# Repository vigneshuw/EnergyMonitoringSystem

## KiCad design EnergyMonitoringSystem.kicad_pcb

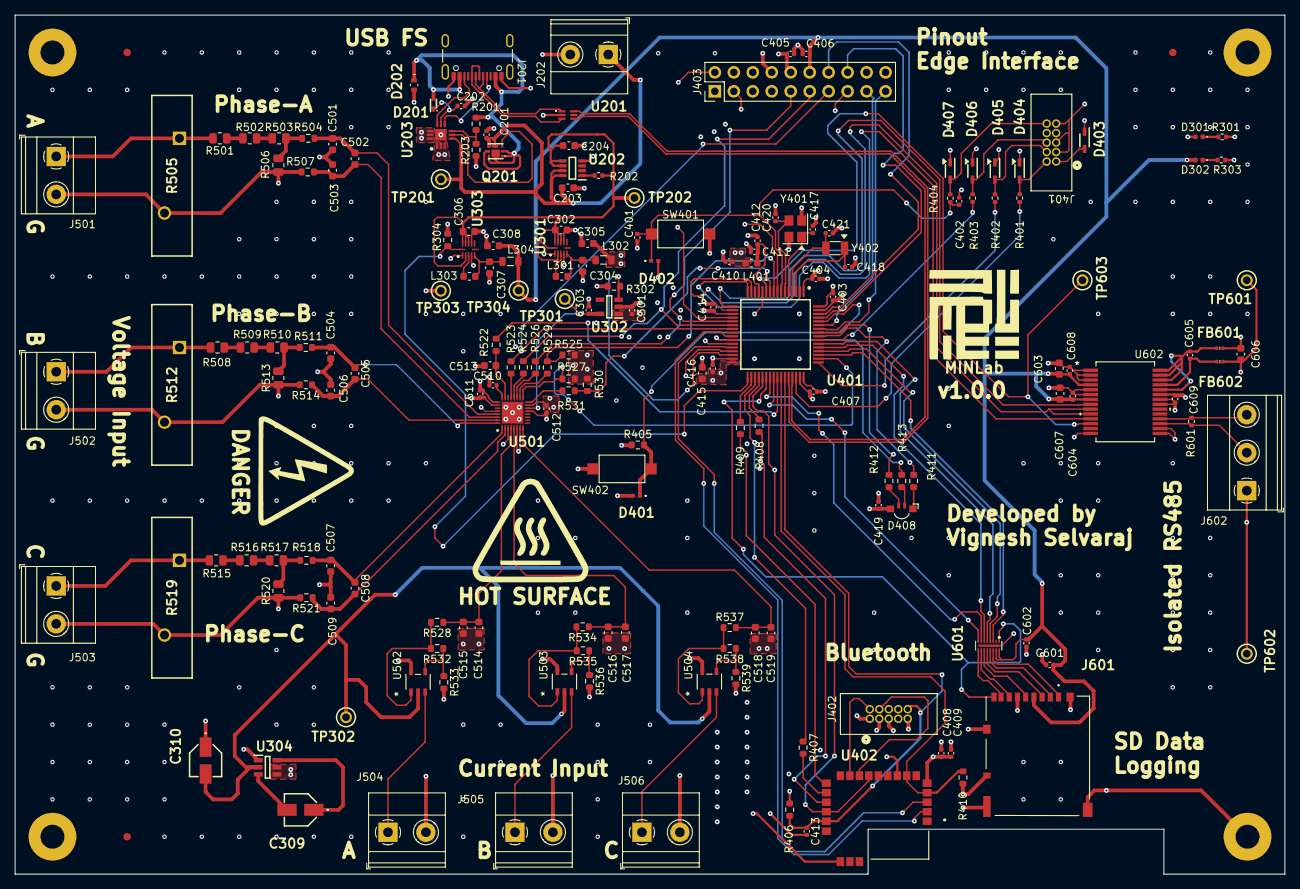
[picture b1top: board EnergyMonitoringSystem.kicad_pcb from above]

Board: 6 copper layers, 170.0 x 115.0 mm, 191 parts (0 on the bottom side), 136 nets.

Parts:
C201, C202, C401, C402, C403, C404, C405, C406, C407, C409, C413, C414, C415, C419, C601, C602: 100n; C_0402_1005Metric
C203, C204, C302, C306, C416, C603, C606, C607: 10u; C_0603_1608Metric
C301, C303, C410, C411, C511, C512: 1u; C_0402_1005Metric
C304, C305, C307, C308: 47u; C_0603_1608Metric
C309, C310: 10u; 10SVPS10M
C408: 2u2; C_0402_1005Metric
C412: 10n; C_0402_1005Metric
C417, C420: 6p8; C_0402_1005Metric
C418, C421: 5p6; C_0402_1005Metric
C501, C503, C504, C506, C507, C509, C513, C514, C516, C518: 10p; C_0603_1608Metric
C502, C505, C508, C515, C517, C519: 6800p; C_0603_1608Metric
C510: 220n; C_0402_1005Metric
C604, C605, C608, C609: 0.1u; C_0402_1005Metric
D201: BAT30KFILM
D202: ESDA7P60-1U1M
D301, D302: LED; LED_0402_1005Metric
D401, D402: ESDALC6V1-1M2; ESDALC6V11M2
D403, D404, D405, D406, D407: PESD3V3L1BA,115; PESD3V3L1BA_115-SOD-323-2
D408: LED_RAGB; LED_Kingbright_APFA3010_3x1.5mm_Horizontal
FB601, FB602: FerriteBead; BLM15HD182SN1D
FM201, FM202, FM203: Fiducial; Fiducial_1mm_Mask2mm
H201, H202, H203, H204: MountingHole_Pad; MountingHole_3.2mm_M3_Pad
J201: USB_C_Receptacle_USB2.0_16P; USB_C_Receptacle_GCT_USB4105-xx-A_16P_TopMnt_Horizontal
J202, J501, J502, J503, J504, J505, J506: Screw_Terminal_01x02; TerminalBlock_Phoenix_MKDS-1,5-2-5.08_1x02_P5.08mm_Horizont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
J401, J402: Conn_02x05_Counter_Clockwise; 62701021621
J403: Conn_02x08_Counter_Clockwise; PinHeader_2x10_P2.54mm_Vertical
J601: DM3AT-SF-PEJM5_40_; DM3ATSFPEJM540
J602: Screw_Terminal_01x03; TerminalBlock_Phoenix_MKDS-1,5-3-5.08_1x03_P5.08mm_Horizont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
L301, L303: 2u2; L_0603_1608Metric
L302, L304: 10u; L_0805_2012Metric
L401: 10n; L_0603_1608Metric
Q201: STL6N3LLH6
R201, R405, R525, R533, R536, R539: 10k; R_0603_1608Metric
R202, R601: 120R; R_0402_1005Metric
R203: 2k7; R_0603_1608Metric
R301, R303: 220R; R_0402_1005Metric
R302, R304, R527, R530: 100k; R_0603_1608Metric
R401, R402, R403, R404: 49R9; R_0402_1005Metric
R406: 4k7; R_0603_1608Metric
R407, R408, R409: 22R; R_0603_1608Metric
R410: 47k; R_0603_1608Metric
R411, R412, R413, R504, R507, R511, R514, R518, R521: 1k; R_0603_1608Metric
R501, R502, R503, R508, R509, R510, R515, R516, R517: 330k; R_0805_2012Metric
R505, R512, R519: R_Variable; B72220S0271K101
R506, R513, R520: 750R; R_0805_2012Metric
R522, R523, R524, R526, R529, R531: 33R; R_0603_1608Metric
R528, R534, R537: 2k; R_0603_1608Metric
R532, R535, R538: 15k; R_0603_1608Metric
SW401, SW402: SW_Push; SW_SPST_CK_RS282G05A3
TP201, TP202, TP301, TP302, TP303, TP304, TP601, TP602, TP603: TestPoint; 5000
U201: USBLC6-2P6; USBLC62P6-SOT666-6
U202: STEF05SGR; STEF05SGR-TSOT23-8L
U203: TCPP01-M12; TCPP01-M12-QFN-12L
U301, U303: ST1PS02CQTR
U302: LDLN025M12R; LDLN025M12R-SOT-23-5
U304: LM2664M6_NOPB; LM2664M6_NOPB-SOT-23-6
U401: STM32F103RGT6; STM32F103RGT6-LQFP-64
U402: BLUENRG-M2SA
U501: ADS131M08IRSNR; ADS131M08IRSNR-QFN40
U502, U503, U504: TSV911ILT; TSV911ILT_SOT23-5
U601: EMIF06-MSD02N16
U602: ADM2565EBRNZ; ADM2565EBRNZ-SOIC-28
Y401: 16MHz; Crystal_SMD_3225-4Pin_3.2x2.5mm
Y402: 32.768KHz; Crystal_SMD_3215-2Pin_3.2x1.5mm

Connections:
+1V2: C303.1, TP301.1, U302.5 (OUT), U501.14 (REFIN)
+5V: C204.1, C302.1, C306.1, R202.1, TP202.1, U202.5 (SOURCE_1), U202.6 (SOURCE_2), U301.2 (VIN), U301.9 (D0), U301.10 (D1), U301.11 (D2), U301.12 (EN), U303.2 (VIN), U303.9 (D0), U303.10 (D1), U303.11 (D2)
+5V_EXT: C201.1, C203.1, J202.1, Q201.4 (S_1), Q201.8 (S_2), TP201.1, U202.7 (VCC_1), U202.8 (VCC_2), U203.4 (SOURCE)
+DCDC_1: C301.1, C305.1, C403.1, C404.1, C405.1, C407.1, C408.1, C409.1, C410.1, C414.1, C415.1, C416.1, C419.1, C511.2, C512.2, D301.2 (A), D403.2 (K2), D408.2 (A), J401.1, J402.1, J403.10, L302.2, L401.1, R406.2, R525.2, R527.2, R530.2, SW402.2, TP303.1, U302.1 (IN), U304.4 (SD), U304.5 (V+), U401.1 (VBAT), U401.19 (VDD_4), U401.32 (VDD_1), U401.48 (VDD_2), U401.64 (VDD_3), U402.5 (VIN), U501.15 (AVDD), U501.26 (DVDD), U502.5 (VCC+), U503.5 (VCC+), U504.5 (VCC+)
+DCDC_2: C308.1, C406.1, C601.1, C602.1, C603.1, C604.1, C607.2, C608.2, D302.2 (A), J403.12, J601.4 (VDD), L304.2, TP304.1, U601.15 (VCC), U601.16 (RDATA_VCC), U602.4 (VCC), U602.7 (VIO)
+VBUSc: D201.2 (A), D202.1 (K), J201.A4 (VBUS), J201.A9 (VBUS), J201.B4 (VBUS), J201.B9 (VBUS), Q201.1 (D_1), Q201.2 (D_2), Q201.5 (D_3), Q201.6 (D_4), Q201.7 (D_5), R201.1
+V_ISO: C606.2, C609.1, FB602.2, TP601.1, U602.23 (VISOIN)
-DCDC_1: C310.2, TP302.1, U304.2 (OUT), U502.2 (VCC-), U503.2 (VCC-), U504.2 (VCC-)
/ADC/CLKIN_ADS_T: C513.1, R522.2, U501.23 (XTAL1_CLKIN)
/ADC/CT_PhaseA_Amp_OUT: R528.2, R532.2, U502.1 (OUT)
/ADC/CT_PhaseA_IN: J504.1, U502.3 (IN+)
/ADC/CT_PhaseB_Amp_OUT: R534.2, R535.2, U503.1 (OUT)
/ADC/CT_PhaseB_IN: J505.1, U503.3 (IN+)
/ADC/CT_PhaseC_Amp_OUT: R537.2, R538.2, U504.1 (OUT)
/ADC/CT_PhaseC_IN: J506.1, U504.3 (IN+)
/ADC/DIN_ADS_T: R523.2, U501.21 (DIN)
/ADC/DOUT_ADS_T: R524.2, U501.20 (DOUT)
/ADC/DRDY_ADS_T: R529.2, U501.18 (DRDY_N)
/ADC/I_Phase_A_P: C514.1, C515.1, R528.1, U501.4 (AIN3P)
/ADC/I_Phase_B_P: C516.1, C517.1, R534.1, U501.5 (AIN4P)
/ADC/I_Phase_C_P: C518.1, C519.1, R537.1, U501.8 (AIN5P)
/ADC/SCK_ADS_T: R526.2, U501.19 (SCLK)
/ADC/SYNC_RESET_ADS_T: R531.2, U501.16 (SYNC_RESET_N)
/ADC/V_Phase_A_N: C502.2, C503.2, R507.1, U501.30 (AIN0N)
/ADC/V_Phase_A_P: C501.1, C502.1, R504.1, U501.29 (AIN0P)
/ADC/V_Phase_B_N: C505.2, C506.2, R514.1, U501.31 (AIN1N)
/ADC/V_Phase_B_P: C504.1, C505.1, R511.1, U501.32 (AIN1P)
/ADC/V_Phase_C_N: C508.2, C509.2, R521.1, U501.2 (AIN2N)
/ADC/V_Phase_C_P: C507.1, C508.1, R518.1, U501.1 (AIN2P)
/SDCARD/SD_CLK: J601.5 (CLK), U601.11 (CLK_EX)
/SDCARD/SD_CMD: J601.3 (CMD), U601.12 (CMD_EX)
/SDCARD/SD_DAT0: J601.7 (DAT0), U601.10 (DAT0_EX)
/SDCARD/SD_DAT1: J601.8 (DAT1), U601.9 (DAT1_EX)
/SDCARD/SD_DAT2: J601.1 (DAT2), U601.14 (DAT2_EX)
/SDCARD/SD_DAT3: J601.2 (CD/DAT3), U601.13 (DAT3_EX)
/USB/FSE_I_LIM: R202.2, U202.1 (I_LIM)
/USB/PD_GATE: Q201.3 (G), U203.5 (GATE)
/USB/PD_IN_GD: C202.1, D201.1 (K), U203.8 (IN_GD)
/USB/PD_VBUS_CTRL: R201.2, R203.1, U203.6 (VBUS_CTRL)
/USB/USB_CC1c: J201.A5 (CC1), U203.7 (CC1C)
/USB/USB_CC2c: J201.B5 (CC2), U203.9 (CC2C)
/USB/USB_OTG_D+: J201.A6 (D+), J201.B6 (D+), U201.3 (I/O2_1)
/USB/USB_OTG_D-: J201.A7 (D-), J201.B7 (D-), U201.1 (I/O1_1)
/VR/CHRG_CAP+: C309.1, U304.6 (CAP+)
/VR/CHRG_CAP-: C309.2, U304.3 (CAP-)
/VR/DC1_SW: L301.1, U301.3 (SW)
/VR/DC1_VOUT: C304.1, L301.2, L302.1, U301.5 (VOUT)
/VR/DC2_SW: L303.1, U303.3 (SW)
/VR/DC2_VOUT: C307.1, L303.2, L304.1, U303.5 (VOUT)
/uC/ADC1_IN9: J403.4, U401.27 (PB1)
/uC/ADC1_IN10: J403.6, U401.8 (PC0)
/uC/BLE_INT: R410.2, U401.42 (PA9), U402.4 (DIO5), U402.7 (DIO7/BOOT)
/uC/BLE_RST: C413.1, J402.10, R406.1, U401.43 (PA10), U402.19 (RESETN)
/uC/BLE_SPI_CS: J403.7, U401.37 (PC6), U402.11 (DIO11), U402.18 (DIO1)
/uC/BLE_SWDCLK: J402.4, U402.12 (DIO9)
/uC/BLE_SWDIO: J402.2, U402.13 (DIO10)
/uC/BLE_TEST8: U401.25 (PC5), U402.2 (ADC1)
/uC/BLE_TEST9: U401.28 (PB2), U402.3 (DIO4)
/uC/BOOT0: D401.1 (K), R405.2, SW402.1, U401.60 (BOOT0)
/uC/NRST: C401.1, C402.1, D402.1 (K), R404.1, SW401.1, U401.7 (NRST)
/uC/OSC32_IN: C418.1, U401.3 (PC14-OSC32_IN), Y402.1
/uC/OSC32_OUT: C421.1, U401.4 (PC15-OSC32_OUT), Y402.2
/uC/OSC_IN: C417.1, U401.5 (PD0-OSC_IN), Y401.1
/uC/OSC_OUT: C420.1, U401.6 (PD1-OSC_OUT), Y401.3
/uC/SPI2_MISO: J403.3, R407.1, U401.35 (PB14)
/uC/SPI2_MOSI: J403.5, R408.1, U402.17 (DIO3)
/uC/SPI2_R_MISO: R407.2, U402.16 (DIO2)
/uC/SPI2_R_MOSI: R408.2, U401.36 (PB15)
/uC/SPI2_R_SCK: R409.2, U401.34 (PB13)
/uC/SPI2_SCK: J403.1, R409.1, U402.15 (DIO0)
/uC/SWDCLK: R402.1, U401.49 (PA14)
/uC/SWDIO: R401.1, U401.46 (PA13)
/uC/SWDO: R403.1, U401.55 (PB3)
/uC/TIM3_CH1: R411.2, U401.56 (PB4)
/uC/TIM3_CH2: R412.2, U401.57 (PB5)
/uC/TIM3_CH3: R413.2, U401.26 (PB0)
ADS_CS: J403.15, R527.1, U401.50 (PA15), U501.17 (CS_N)
ADS_DIN_uC_DOUT: J403.13, R523.1, U401.23 (PA7)
ADS_DOUT_uC_DIN: J403.11, R524.1, U401.22 (PA6)
ADS_DRDY: J403.20, R525.1, R529.1, U401.9 (PC1)
ADS_SPI1_SCK: J403.9, R526.1, U401.21 (PA5)
ADS_STM32_CLKOUT: R522.1, U401.41 (PA8)
ADS_SYNC_RESET: R530.1, R531.1, U401.10 (PC2)
DAC_OUT1: J403.2, U401.20 (PA4)
DCDC_2_EN: R304.1, U303.12 (EN), U401.33 (PB12)
GND: C201.2, C202.2, C203.2, C204.2, C301.2, C302.2, C303.2, C304.2, C305.2, C306.2, C307.2, C308.2, C310.1, C401.2, C402.2, C403.2, C404.2, C405.2, C406.2, C407.2, C408.2, C409.2, C410.2, C411.2, C412.2, C413.2, C414.2, C415.2, C416.2, C417.2, C418.2, C419.2, C420.2, C421.2, C501.2, C503.1, C504.2, C506.1, C507.2, C509.1, C510.2, C511.1, C512.1, C513.2, C514.2, C515.2, C516.2, C517.2, C518.2, C519.2, C601.2, C602.2, C603.2, C604.2, C607.1, C608.1, D202.2 (A), D401.2 (A), D402.2 (A), D403.1 (K1), D404.1 (K1), D405.1 (K1), D406.1 (K1), D407.1 (K1), H201.1, H202.1, H203.1, H204.1, J201.A1 (GND), J201.A12 (GND), J201.B1 (GND), J201.B12 (GND), J201.S1 (SHIELD), J202.2, J401.3, J401.5, J401.9, J402.3, J402.5, J402.9, J403.8, J501.2, J502.2, J503.2, J504.2, J505.2, J506.2, J601.6 (VSS), J601.MP1, J601.MP2, J601.MP3, J601.MP4, J601.MP5, R203.2, R301.2, R302.1, R303.2, R304.2, R405.1, R410.1, R505.2, R506.1, R507.2, R512.2, R513.1, R514.2, R519.2, R520.1, R521.2, R533.2, R536.2, R539.2, SW401.2, U201.2 (GND), U202.4 (GND), U203.1 (CC2), U203.2 (GND), U203.3 (CC1), U203.10 (DB/), U203.11 (FLT/), U203.12 (VCC), U203.13 (EP), U301.1 (AUX), U301.4 (GND), U301.8 (CL), U302.2 (GND), U303.1 (AUX), U303.4 (GND), U303.8 (CL), U304.1 (GND), U401.12 (VSSA), U401.18 (VSS_4), U401.31 (VSS_1), U401.47 (VSS_2), U401.63 (VSS_3), U402.8 (GND_1), U402.21 (GND_2), U501.3 (AIN3N), U501.6 (AIN4N), U501.7 (AIN5N), U501.13 (AGND), U501.25 (DGND), U501.28 (AGND), U501.33 (EP), U601.17 (EP_(GND)), U602.1 (GND1), U602.2 (GND1), U602.3 (GND1), U602.5 (GND1), U602.6 (GND1), U602.14 (GND1), Y401.2, Y401.4
GND2: C606.1, C609.2, FB601.2, J602.1, TP602.1, U602.15 (GND2), U602.16 (GND2), U602.21 (GND2), U602.22 (GND2)
GPIO1_Input: J403.17, U401.59 (PB7)
GPIO1_Output: J403.18, U401.29 (PB10)
GPIO2_Input: J403.19, U401.58 (PB6)
I2C1_SCL: J403.16, U401.61 (PB8)
I2C1_SDA: J403.14, U401.62 (PB9)
LDO_EN: R302.2, U302.3 (EN), U401.30 (PB11)
unnamed: D301.1 (K), R301.1
unnamed: D302.1 (K), R303.1
unnamed: D404.2 (K2), J401.2, R401.2
unnamed: D405.2 (K2), J401.4, R402.2
unnamed: D406.2 (K2), J401.6, R403.2
unnamed: D407.2 (K2), J401.10, R404.2
unnamed: D408.4 (BK), R413.1
unnamed: D408.3 (GK), R412.1
unnamed: D408.1 (RK), R411.1
unnamed: J501.1, R501.2, R505.1
unnamed: J502.1, R508.2, R512.1
unnamed: J503.1, R515.2, R519.1
unnamed: J602.2, R601.1, U602.17 (A)
unnamed: J602.3, R601.2, U602.18 (B)
unnamed: R501.1, R502.2
unnamed: R502.1, R503.2
unnamed: R503.1, R504.2, R506.2
unnamed: R508.1, R509.2
unnamed: R509.1, R510.2
unnamed: R510.1, R511.2, R513.2
unnamed: R515.1, R516.2
unnamed: R516.1, R517.2
unnamed: R517.1, R518.2, R520.2
unnamed: C510.1, U501.24 (CAP)
unnamed: R532.1, R533.1, U502.4 (IN-)
unnamed: R535.1, R536.1, U503.4 (IN-)
unnamed: R538.1, R539.1, U504.4 (IN-)
unnamed: C605.2, FB602.1, U602.25 (VISOOUT)
unnamed: C605.1, FB601.1, U602.24 (GNDISO), U602.26 (GNDISO), U602.27 (VSEL), U602.28 (GNDISO)
SDMMC_CK: U401.53 (PC12), U601.6 (CLK_IN)
SDMMC_CMD: U401.54 (PD2), U601.5 (CMD_IN)
SDMMC_D0: U401.39 (PC8), U601.7 (DAT0_IN)
SDMMC_D1: U401.40 (PC9), U601.8 (DAT1_IN)
SDMMC_D2: U401.51 (PC10), U601.3 (DAT2_IN)
SDMMC_D3: U401.52 (PC11), U601.4 (DAT3_IN)
SD_DETECT: J601.CD1 (CARD_DETECT), U401.38 (PC7), U601.1 (WP/CD)
UART_INV_485: TP603.1, U401.11 (PC3), U602.12 (INV)
UART_RTS_485: U401.15 (PA1), U602.9 (*RE), U602.10 (DE)
UART_RX_485: U401.17 (PA3), U602.8 (RXD)
UART_TX_485: U401.16 (PA2), U602.11 (TXD)
VDDA: C411.1, C412.1, L401.2, U401.13 (VDDA)
uC_OTG_D+: U201.4 (I/O2_2), U401.45 (PA12)
uC_OTG_D-: U201.6 (I/O1_2), U401.44 (PA11)

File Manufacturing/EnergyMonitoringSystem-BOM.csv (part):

"Reference","Value","Datasheet","Footprint","Qty","DNP","Manufacturer_Name","Manufacturer_Part_Number","Distributor_Link"
"J601","DM3AT-SF-PEJM5_40_","https://componentsearchengine.com/Datasheets/2/DM3AT-SF-PEJM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","EMS:DM3ATSFPEJM540","1","","Hirose","DM3AT-SF-PEJM5(40)","https://www.mouser.co.uk/ProductDetail/Hirose-Connector/DM3A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"
"D403","PESD3V3L1BA,115","https://assets.nexperia.com/documents/data-sheet/PESDXL1BA_SER.pdf","EMS:PESD3V3L1BA_115-SOD-323-2","1","","Nexperia","PESD3V3L1BA,115","https://www.mouser.co.uk/ProductDetail/Nexperia/PESD3V3L1BA1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"
"D404","PESD3V3L1BA,115","https://assets.nexperia.com/documents/data-sheet/PESDXL1BA_SER.pdf","EMS:PESD3V3L1BA_115-SOD-323-2","1","","Nexperia","PESD3V3L1BA,115","https://www.mouser.co.uk/ProductDetail/Nexperia/PESD3V3L1BA1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"
"D405","PESD3V3L1BA,115","https://assets.nexperia.com/documents/data-sheet/PESDXL1BA_SER.pdf","EMS:PESD3V3L1BA_115-SOD-323-2","1","","Nexperia","PESD3V3L1BA,115","https://www.mouser.co.uk/ProductDetail/Nexperia/PESD3V3L1BA1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"
"D406","PESD3V3L1BA,115","https://assets.nexperia.com/documents/data-sheet/PESDXL1BA_SER.pdf","EMS:PESD3V3L1BA_115-SOD-323-2","1","","Nexperia","PESD3V3L1BA,115","https://www.mouser.co.uk/ProductDetail/Nexperia/PESD3V3L1BA1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"
"D407","PESD3V3L1BA,115","https://assets.nexperia.com/documents/data-sheet/PESDXL1BA_SER.pdf","EMS:PESD3V3L1BA_115-SOD-323-2","1","","Nexperia","PESD3V3L1BA,115","https://www.mouser.co.uk/ProductDetail/Nexperia/PESD3V3L1BA1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"
"D201","BAT30KFILM","http://www.st.com/content/ccc/resource/technical/document/da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","EMS:BAT30KFILM","1","","STMicroelectronics","BAT30KFILM","https://www.mouser.co.uk/ProductDetail/STMicroelectronics/BA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"
"U402","BLUENRG-M2SA","https://www.st.com/resource/en/datasheet/bluenrg-m2.pdf","EMS:BLUENRG-M2SA","1","","STMicroelectronics","BLUENRG-M2SA","https://www.mouser.co.uk/ProductDetail/STMicroelectronics/BL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"
"U601","EMIF06-MSD02N16","http://www.st.com/content/ccc/resource/technical/document/da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","EMS:EMIF06-MSD02N16","1","","STMicroelectronics","EMIF06-MSD02N16","https://www.mouser.co.uk/ProductDetail/STMicroelectronics/EM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"
"D202","ESDA7P60-1U1M","https://www.st.com/resource/en/datasheet/esda7p60-1u1m.pdf","EMS:ESDA7P60-1U1M","1","","STMicroelectronics","ESDA7P60-1U1M","https://www.mouser.co.uk/ProductDetail/STMicroelectronics/ES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"
"D401","ESDALC6V1-1M2","","EMS:ESDALC6V11M2","1","","STMicroelectronics","ESDALC6V1-1M2","https://www.mouser.co.uk/ProductDetail/STMicroelectronics/ES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"
"D402","ESDALC6V1-1M2","","EMS:ESDALC6V11M2","1","","STMicroelectronics","ESDALC6V1-1M2","https://www.mouser.co.uk/ProductDetail/STMicroelectronics/ES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"
"U302","LDLN025M12R","https://www.st.com/resource/en/datasheet/ldln025.pdf","EMS:LDLN025M12R-SOT-23-5","1","","STMicroelectronics","LDLN025M12R","https://www.mouser.co.uk/ProductDetail/STMicroelectronics/LD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"
"U301","ST1PS02CQTR","https://www.st.com/en/power-management/st1ps02.html","EMS:ST1PS02CQTR","1","","STMicroelectronics","ST1PS02CQTR","https://www.mouser.co.uk/ProductDetail/STMicroelectronics/ST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"
"U303","ST1PS02CQTR","https://www.st.com/en/power-management/st1ps02.html","EMS:ST1PS02CQTR","1","","STMicroelectronics","ST1PS02CQTR","https://www.mouser.co.uk/ProductDetail/STMicroelectronics/ST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"
"U202","STEF05SGR","https://www.st.com/resource/en/datasheet/stef05s.pdf","EMS:STEF05SGR-TSOT23-8L","1","","STMicroelectronics","STEF05SGR","https://www.mouser.co.uk/ProductDetail/STMicroelectronics/ST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"
"Q201","STL6N3LLH6","https://www.st.com/resource/en/datasheet/stl6n3llh6.pdf","EMS:STL6N3LLH6","1","","STMicroelectronics","STL6N3LLH6","https://www.mouser.co.uk/ProductDetail/STMicroelectronics/ST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"
"U401","STM32F103RGT6","https://4donline.ihs.com/images/VipMasterIC/IC/SGST/SGST-S-A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","EMS:STM32F103RGT6-LQFP-64","1","","STMicroelectronics","STM32F103RGT6","https://www.mouser.co.uk/ProductDetail/STMicroelectronics/ST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"
"U203","TCPP01-M12","https://www.st.com/resource/en/datasheet/tcpp01-m12.pdf","EMS:TCPP01-M12-QFN-12L","1","","STMicroelectronics","TCPP01-M12","https://www.mouser.co.uk/ProductDetail/STMicroelectronics/TC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"
"U201","USBLC6-2P6","https://datasheet.lcsc.com/szlcsc/STMicroelectronics-USBLC6-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","EMS:USBLC62P6-SOT666-6","1","","STMicroelectronics","USBLC6-2P6","https://www.mouser.co.uk/ProductDetail/STMicroelectronics/US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"
"U304","LM2664M6_NOPB","https://datasheet.datasheetarchive.com/originals/distributor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","EMS:LM2664M6_NOPB-SOT-23-6","1","","Texas Instruments","LM2664M6/NOPB","https://www.mouser.co.uk/ProductDetail/Texas-Instruments/LM2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"
"L401","10n","https://www.mouser.com/datasheet/2/3/AISC_0603HP-3317970.pdf","Inductor_SMD:L_0603_1608Metric","1","","ABRACON","AISC-0603HP-10NJ-T","https://www.mouser.com/ProductDetail/ABRACON/AISC-0603HP-10N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"
"U602","ADM2565EBRNZ","https://www.mouser.com/datasheet/2/609/adm2561e_adm2563e_adm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","EMS:ADM2565EBRNZ-SOIC-28","1","","Analog Devices","ADM2565EBRNZ","https://www.mouser.com/ProductDetail/Analog-Devices/ADM2565E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"
"SW401","SW_Push","https://www.mouser.com/datasheet/2/240/RS_282G05A_SM_RT-3051254.pdf","Button_Switch_SMD:SW_SPST_CK_RS282G05A3","1","","C&K","RS282G05A3SMRT","https://www.mouser.com/ProductDetail/CK/RS282G05A3SMRT?qs=Gu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"
"SW402","SW_Push","https://www.mouser.com/datasheet/2/240/RS_282G05A_SM_RT-3051254.pdf","Button_Switch_SMD:SW_SPST_CK_RS282G05A3","1","","C&K","RS282G05A3SMRT","https://www.mouser.com/ProductDetail/CK/RS282G05A3SMRT?qs=Gu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"
"R505","R_Variable","https://product.tdk.com/system/files/dam/doc/product/protect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","EMS:B72220S0271K101","1","","EPCOS/TDK","B72220S0271K101","https://www.mouser.com/ProductDetail/EPCOS-TDK/B72220S0271K1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"
"R512","R_Variable","https://product.tdk.com/system/files/dam/doc/product/protect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","EMS:B72220S0271K101","1","","EPCOS/TDK","B72220S0271K101","https://www.mouser.com/ProductDetail/EPCOS-TDK/B72220S0271K1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"
"R519","R_Variable","https://product.tdk.com/system/files/dam/doc/product/protect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","EMS:B72220S0271K101","1","","EPCOS/TDK","B72220S0271K101","https://www.mouser.com/ProductDetail/EPCOS-TDK/B72220S0271K1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"
"J403","Conn_02x08_Counter_Clockwise","~","Connector_PinHeader_2.54mm:PinHeader_2x10_P2.54mm_Vertical","1","","Harwin","M20-9720546","https://www.mouser.com/ProductDetail/Harwin/M20-9720546?qs=v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"
"J201","USB_C_Receptacle_USB2.0_16P","https://www.usb.org/sites/default/files/documents/usb_type-c.zip","Connector_USB:USB_C_Receptacle_GCT_USB4105-xx-A_16P_TopMnt_Horizontal","1","","Hirose Connector","CX90B-16P","https://www.mouser.com/ProductDetail/Hirose-Connector/CX90B-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"
"TP201","TestPoint","https://www.mouser.com/datasheet/2/215/000-5004-741320.pdf","EMS:5000","1","","Keystone Electronics","5000","https://www.mouser.com/ProductDetail/Keystone-Electronics/50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"
"TP202","TestPoint","https://www.mouser.com/datasheet/2/215/000-5004-741320.pdf","EMS:5000","1","","Keystone Electronics","5000","https://www.mouser.com/ProductDetail/Keystone-Electronics/50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"
"TP301","TestPoint","https://www.mouser.com/datasheet/2/215/000-5004-741320.pdf","EMS:5000","1","","Keystone Electronics","5000","https://www.mouser.com/ProductDetail/Keystone-Electronics/50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"
"TP302","TestPoint","https://www.mouser.com/datasheet/2/215/000-5004-741320.pdf","EMS:5000","1","","Keystone Electronics","5000","https://www.mouser.com/ProductDetail/Keystone-Electronics/50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"
"TP303","TestPoint","https://www.mouser.com/datasheet/2/215/000-5004-741320.pdf","EMS:5000","1","","Keystone Electronics","5000","https://www.mouser.com/ProductDetail/Keystone-Electronics/50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"
"TP304","TestPoint","https://www.mouser.com/datasheet/2/215/000-5004-741320.pdf","EMS:5000","1","","Keystone Electronics","5000","https://www.mouser.com/ProductDetail/Keystone-Electronics/50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"
"TP601","TestPoint","https://www.mouser.com/datasheet/2/215/000-5004-741320.pdf","EMS:5000","1","","Keystone Electronics","5000","https://www.mouser.com/ProductDetail/Keystone-Electronics/50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"
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
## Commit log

2024-09-05 with battery management
2024-09-05 only usb powered
2024-09-06 components with distributor links added
2024-09-06 minor improvements to net labeling
2024-09-20 OpAmp Simulation
2024-09-21 bacis pcb configuration
2024-09-21 added netclasses
2024-09-23 pcb layout init
    1. Pulled all items from schematics
    2. Set board stackup and constraints
    3. Create polygon pours for power and ground
    4. Created isolated ground and power
2024-09-23 routed board power supply
    1. USB
    2. LDO for DCDC_1 and DCDC_2
    3. LDO for +1V2
2024-09-24 routing of CTs complete
2024-09-24 adc wiring complete
2024-09-24 power supply to uC
    1. Power supply complete
    2. Crystal Oscillator complete
2024-09-24 adc to uc complete
2024-09-24 routing for blueNRG complete
2024-09-26 all connections complete
2024-09-26 erc with no error
    1. Updated footprint for ADS
    2. fixed constraints
2024-09-27 minor updates
2024-09-30 added some silkscreen texts and logos
2024-09-30 updated all via sizes
2024-10-14 change in opAmp config
2024-10-14 update to OpAmp setup and bug fix
    1. Fixed incorrect opamp connection
    2. Improved RF connectivity for BLE
    3. Fixed minor bugs
2024-10-14 keep out zones for copper fills added
2024-10-15 updated mounting point and fiducial locations
2024-10-19 stitching vias and added power LEDs
2024-10-19 removed unused via pads
2024-10-19 fixed some clearance violation
2024-10-19 added BOM
2024-12-12 finalized design v1.0.0
2025-03-13 added readme
    Future Updates Planned
2025-03-13 downloaded step files
2025-08-08 v2.0 started
2025-10-11 v2.0 schematics updated
    1. Need to be tested for errors
    2. PCB layout is not started yet
2025-10-11 minor formatting updates
2025-10-12 schematics errors fixed and ready for PCB
2025-10-13 minor annotation change
2025-10-29 new version created. Now at v2.0.0
2025-10-29 fixed the diff impedance error
2025-11-01 validation BOM
2025-11-02 optimized the eMMC routing
2025-11-03 finetune ethernet lines
2025-11-04 fine tune high speed traces
2025-11-05 finetuned design - added stitching vias
2025-11-05 updated keep out issue
2025-11-12 minor design improvements
2025-11-12 solder bridge fixed
2025-11-12 minor trace fine tune
2025-11-13 removed solder bridges
